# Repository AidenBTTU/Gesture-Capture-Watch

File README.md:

# Gesture-Capture-Watch
A wristband-mounted gesture recognition system built around an STM32F411, IMU, and OLED display, with USB-C battery charging and ESD-protected I/O. Includes full PCB design, manufacturing files, and firmware for real-time motion capture and on-device gesture classification via TFLite Micro. 

# Hardware Overview
- **MCU:** [STM32F411CEU6](https://www.st.com/en/microcontrollers-microprocessors/stm32f411.html), high Flash and SRAM to run TFLite model
- **IMU:** [LSM6DSOX](https://www.st.com/en/mems-and-sensors/lsm6dsox.html), industry standard, small form factor, low power consumption, includes a machine learning core for pre-processing
- **Power System:**
  - **Interface:** [USB-C](https://www.digikey.com/en/products/detail/gct/USB4105-GF-A-120/14559037), flexible power delivery, industry standard
  - **ESD Protection:** [USBLC6-2SC6](https://www.digikey.com/en/products/detail/stmicroelectronics/USBLC6-2SC6/1040559), industry standard
  - **Li-ion Battery Charger:** [BQ24092DGQR](https://www.ti.com/product/BQ24092/part-details/BQ24092DGQR), short circuit protection, variable charging
  - **Linear Regulator:** [TPS7A0533PDBZ](https://www.ti.com/product/TPS7A05/part-details/TPS7A0533PDBZT), low drop-out
- **Display:** 0.96" OLED display with SSD1306 chipset

# Software Overview (WIP)
- **Programming Environment:** STM32 programmed and configured via STLink V2. STM32CubeIDE was used to write code in C, and STM32CubeMX was used to set up peripherals and the external high-speed clock.
- **Libraries:** [u8g2](https://github.com/olikraus/u8g2), [lsm6dsox](https://github.com/STMicroelectronics/lsm6dsox-pid)

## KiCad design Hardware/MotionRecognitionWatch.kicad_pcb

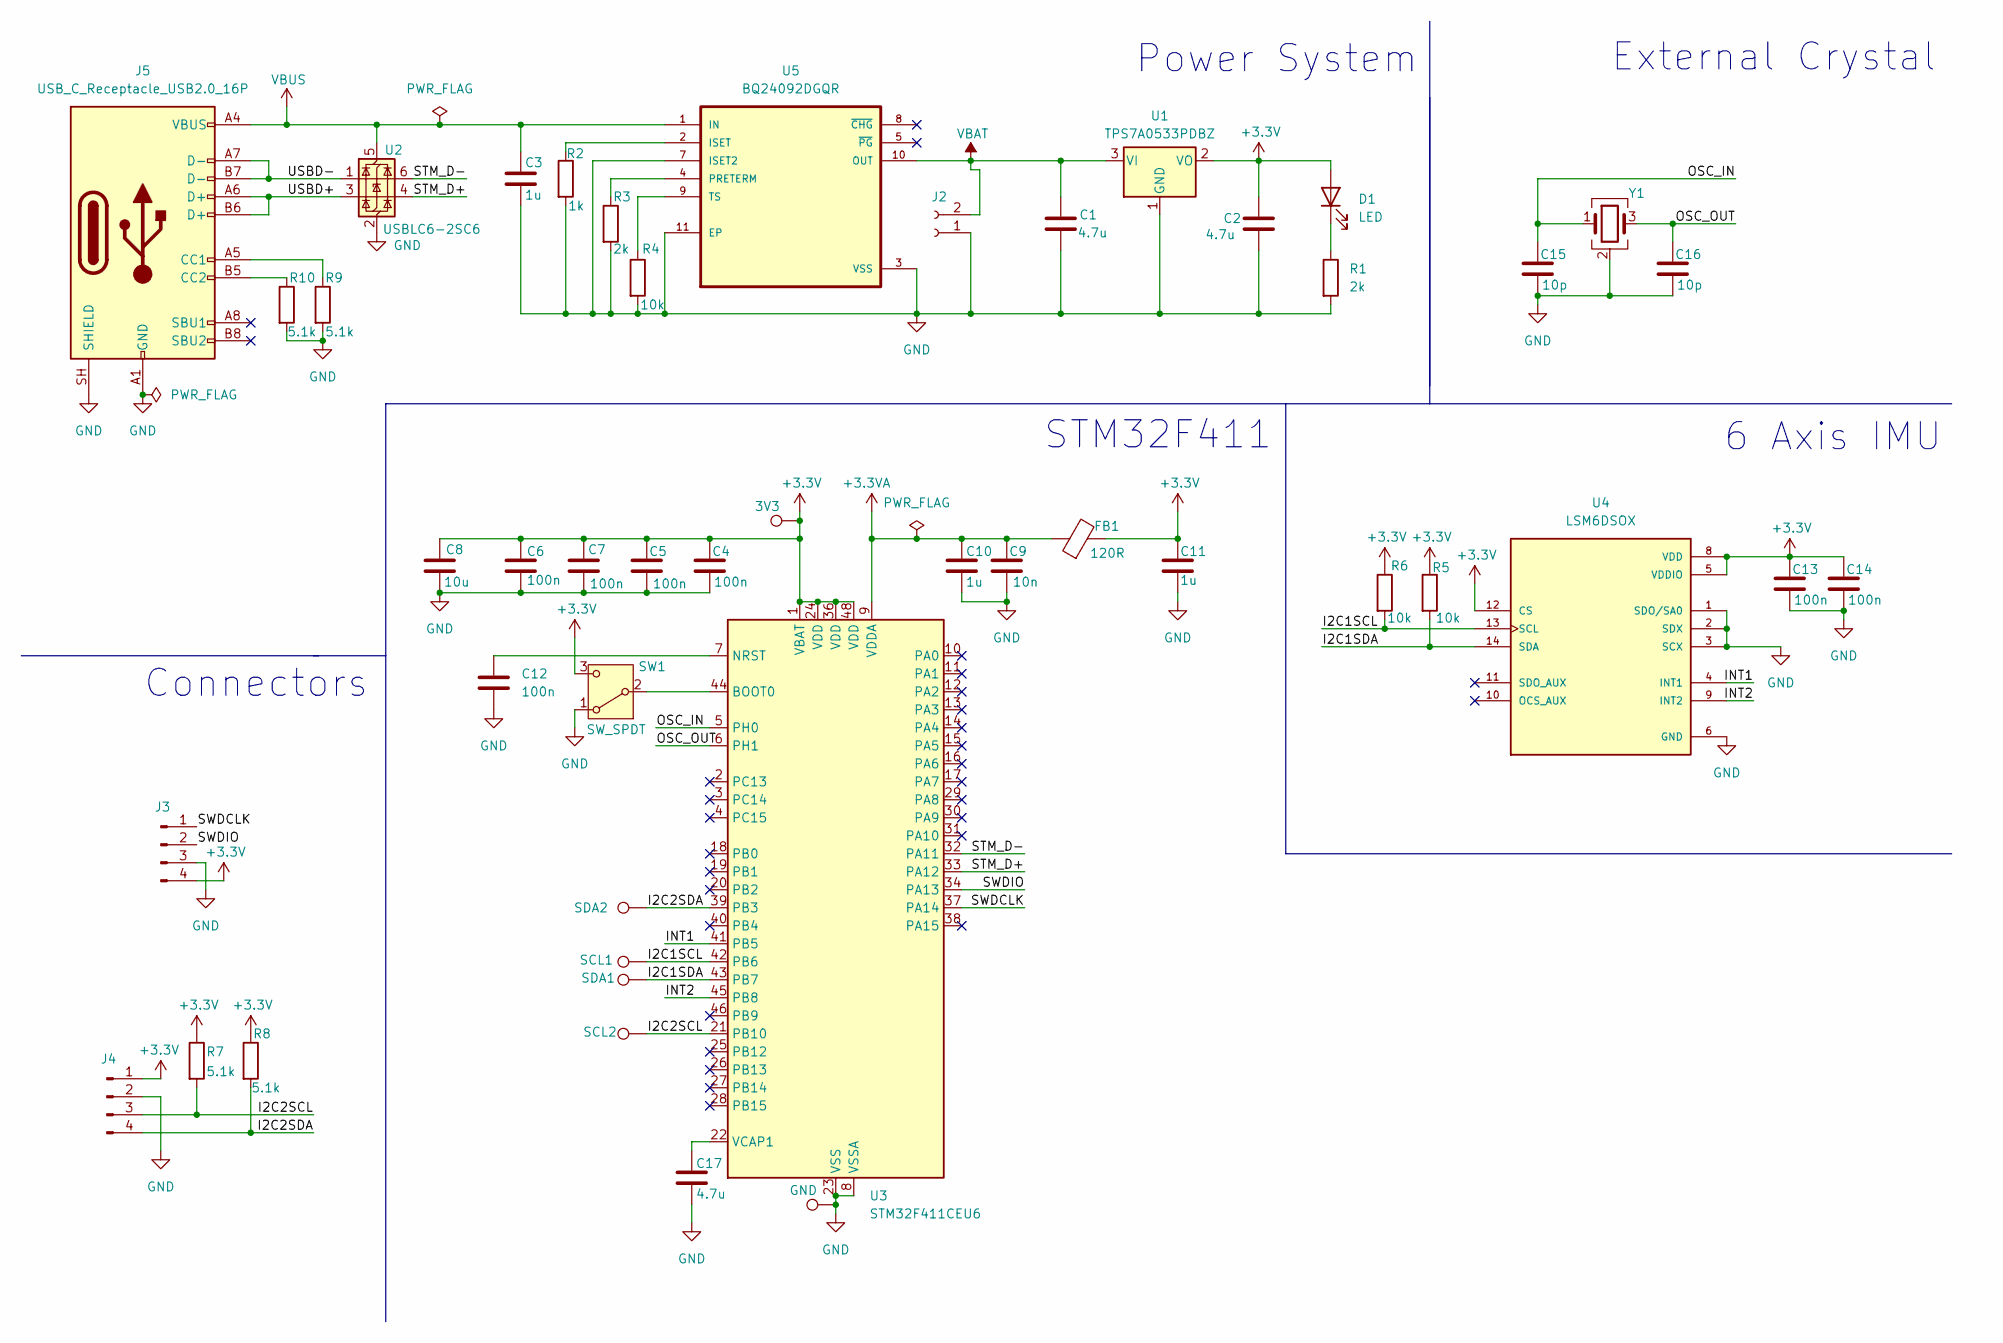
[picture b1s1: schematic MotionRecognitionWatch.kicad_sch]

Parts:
3V3: TestPoint; TestPoint_Pad_2.0x2.0mm
C1, C2, C17: 4.7u; C_0603_1608Metric
C3, C10, C11: 1u; C_0603_1608Metric
C4, C5, C6, C7, C12, C13, C14: 100n; C_0402_1005Metric
C8: 10u; C_0603_1608Metric
C9: 10n; C_0402_1005Metric
C15, C16: 10p; C_0402_1005Metric
D1: LED; LED_0603_1608Metric
FB1: 120R; L_0603_1608Metric
GND: TestPoint; TestPoint_Pad_2.0x2.0mm
J2: Conn_01x02_Socket; JST_PH_S2B-PH-K_1x02_P2.00mm_Horizontal
J3, J4: Conn_01x04_Pin; PinHeader_1x04_P2.54mm_Vertical
J5: USB_C_Receptacle_USB2.0_16P; USB_C_Receptacle_GCT_USB4105-xx-A_16P_TopMnt_Horizontal
R1, R3: 2k; R_0402_1005Metric
R2: 1k; R_0402_1005Metric
R4, R5, R6: 10k; R_0402_1005Metric
R7, R8, R9, R10: 5.1k; R_0402_1005Metric
SCL1, SCL2: TestPoint; TestPoint_Pad_2.0x2.0mm
SDA1: TestPoint; TestPoint_Pad_2.0x2.0mm
SDA2: TestPoint_Pad_2.0x2.0mm
SW1: SW_SPDT; SW_SPDT_PCM12
U1: TPS7A0533PDBZ; SOT-23
U2: USBLC6-2SC6; SOT-23-6
U3: STM32F411CEU6; QFN-48-1EP_7x7mm_P0.5mm_EP5.6x5.6mm
U4: LSM6DSOX; PQFN50P250X300X86-14N; PARTREV 3.0
U5: BQ24092DGQR; IC_XTR111AIDGQR
Y1: Crystal_GND24; Crystal_SMD_3225-4Pin_3.2x2.5mm

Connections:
+3.3V: 3V3.1 (1_1), C2.1, C4.1, C5.1, C6.1, C7.1, C8.1, C11.1, C13.1, C14.1, D1.2 (A), FB1.2, J3.4, J4.1, R5.1, R6.1, R7.1, R8.1, SW1.3 (C), U1.2 (VO), U3.1 (VBAT), U3.24 (VDD), U3.36 (VDD), U3.48 (VDD), U4.5 (VDDIO), U4.8 (VDD), U4.12 (CS); also elsewhere on the board
+3.3VA: C9.1, C10.1, FB1.1, U3.9 (VDDA)
/I2C1SCL: R6.2, SCL1.1 (1_1), U3.42 (PB6), U4.13 (SCL); also elsewhere on the board
/I2C1SDA: R5.2, SDA1.1 (1_1), U3.43 (PB7), U4.14 (SDA); also elsewhere on the board
/I2C2SCL: J4.3, R7.2, SCL2.1 (1_1), U3.21 (PB10)
/I2C2SDA: J4.4, R8.2, SDA2.1 (1_1), U3.39 (PB3)
/INT1: U3.41 (PB5), U4.4 (INT1); also elsewhere on the board
/INT2: U3.45 (PB8), U4.9 (INT2); also elsewhere on the board
/OSC_IN: C15.1, U3.5 (PH0), Y1.1
/OSC_OUT: C16.1, U3.6 (PH1), Y1.3
/STM_D+: U2.4 (I/O2), U3.33 (PA12)
/STM_D-: U2.6 (I/O1), U3.32 (PA11)
/SWDCLK: J3.1, U3.37 (PA14)
/SWDIO: J3.2, U3.34 (PA13)
/USBD+: J5.A6 (D+), J5.B6 (D+), U2.3 (I/O2)
/USBD-: J5.A7 (D-), J5.B7 (D-), U2.1 (I/O1)
GND: C1.2, C2.2, C3.2, C4.2, C5.2, C6.2, C7.2, C8.2, C9.2, C10.2, C11.2, C12.2, C13.2, C14.2, C15.2, C16.2, C17.2, GND.1 (1_1), J2.1, J3.3, J4.2, J5.A1 (GND), J5.A12 (GND), J5.B1 (GND), J5.B12 (GND), J5.SH (SHIELD), R1.2, R2.2, R3.2, R4.2, R9.2, R10.2, SW1.1 (A), U1.1 (GND), U2.2 (GND), U3.8 (VSSA), U3.23 (VSS), U3.35 (VSS), U3.47 (VSS), U3.49 (VSS), U4.1 (SDO/SA0), U4.2 (SDX), U4.3 (SCX), U4.6 (GND), U4.7 (GND), U5.3 (VSS), U5.7 (ISET2), U5.11 (EP), U5.12, U5.13, U5.14, U5.15, U5.16, Y1.2 (G), Y1.4 (G); also elsewhere on the board
unnamed: D1.1 (K), R1.1
unnamed: J5.A5 (CC1), R9.1
unnamed: J5.B5 (CC2), R10.1
unnamed 20: SW1.2 (B), U3.44 (BOOT0); also elsewhere on the board
unnamed: C12.1, U3.7 (NRST)
unnamed: C17.1, U3.22 (VCAP1)
unnamed: R2.1, U5.2 (ISET)
unnamed: R3.1, U5.4 (PRETERM)
unnamed: R4.1, U5.9 (TS)
VBAT: C1.1, J2.2, U1.3 (VI), U5.10 (OUT)
VBUS: C3.1, J5.A4 (VBUS), J5.A9 (VBUS), J5.B4 (VBUS), J5.B9 (VBUS), U2.5 (VBUS), U5.1 (IN)

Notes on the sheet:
STM32F411
Power System
Connectors
6 Axis IMU
External Crystal

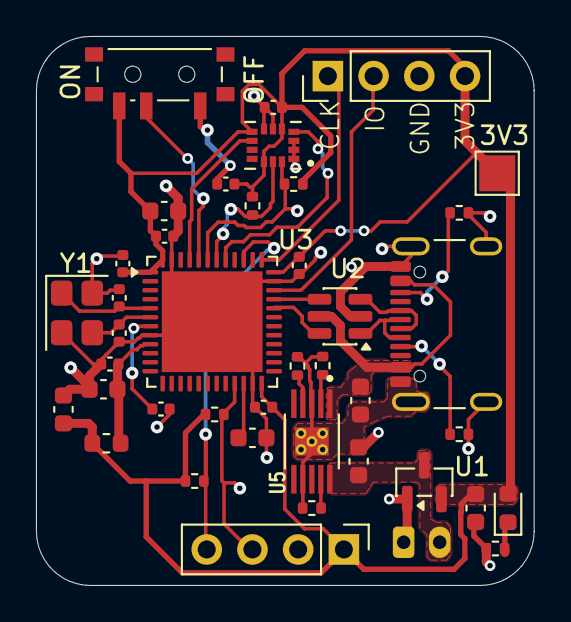
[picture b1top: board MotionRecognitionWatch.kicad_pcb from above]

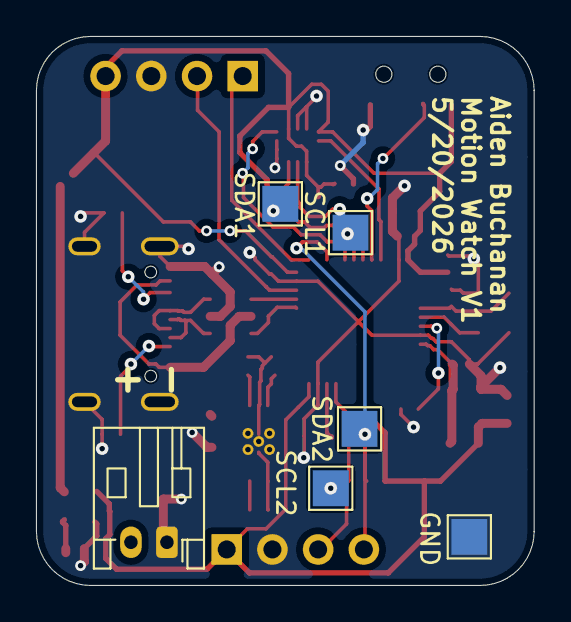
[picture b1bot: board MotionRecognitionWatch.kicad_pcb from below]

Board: 2 copper layers, 27.6 x 30.5 mm, 46 parts (6 on the bottom side), 28 nets.

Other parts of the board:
ON: SW_SPDT; SW_SPDT_PCM12
U6: LSM6DSOX; PQFN50P250X300X86-14N

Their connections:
+3.3V: ON.3 (C), U6.5 (VDDIO), U6.8 (VDD), U6.12 (CS); also elsewhere on the board
/I2C1SCL: U6.13 (SCL); also elsewhere on the board
/I2C1SDA: U6.14 (SDA); also elsewhere on the board
/INT1: U6.4 (INT1); also elsewhere on the board
/INT2: U6.9 (INT2); also elsewhere on the board
GND: ON.1 (A), U6.1 (SDO/SA0), U6.2 (SDX), U6.3 (SCX), U6.6 (GND), U6.7 (GND); also elsewhere on the board
unnamed 20: ON.2 (B); also elsewhere on the board
